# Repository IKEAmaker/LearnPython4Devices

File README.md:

# Learn to Code Python For a Device
Hej!

We have put together a few kits of a tiny microcontroller, a small LED matrix and a joystick.
There is also a [step by step guide on how to get started with coding](https://github.com/IKEAmaker/LearnPython4Devices/raw/master/Docs/LearnToCode-CompleteGuide.pdf) with this kit.
The target audience for this kit is 100% analog humans with zero coding experience.
We hope this is a fun way to get into digital creativity.

If you want to get an idea how this kit can be used to teach coding,
you can check [this 6 minute video.](https://youtu.be/odnBymFynmI)

One of the projects in the guide includes a scrolling text display:

# Build This Kit
If you can come to Maker Friday at the Co-Create lab and we'll help you out.
Most of the kit can be bought from Adafruit. We have set up a [shopping list that covers almost everything needed.](http://www.adafruit.com/wishlists/482690) The only thing you need to add is some strips of wires.

| How to build |               | 
| ------------- |:-------------:|
|This is what the kit looks like when it is built|  |
| The first step is to collect all the parts ||
| The next step is to solder the rows of pins and the LED matrix to the PCBs. There are a few videos showing how it's done: [1 Solder the microcontroller to it's rows of pins (and some general soldering tips)](https://www.youtube.com/watch?v=GbWMCBHOKaM). [2 Solder the LED matrix to it's own PCB](https://www.youtube.com/watch?v=Tg6XQbmof4U). [3 Solder a row of pins to the LED matrix PCB](https://www.youtube.com/watch?v=a5eWrJ8vEno)  ||
| When all the soldering is done, we insert the components into the breadboard and then its time to wire things up. The image to the right is a schematic showing how to connect the different signals.||
| The first wires to connect are the power wires to both the LED matrix and the Joystick. The red wire connects "3V" pin on the microcontroller with "+" pin on the LED matrix and "+5V" pin on the joystick. The black wire connects "Gnd" pin on the microcontroller with "-" pin on the LED matrix and "GND" pin on the joystick.  ||
| Next we connect the "C" pin on the LED matrix to pin "2" on the microcontroller. And the "D" pin on the LED matrix is connected to "0" pin on the microcontroller.  ||
| Lastly we connect three signals between the microcontroller and the joystick. The "VRx" pin on the joystick should be connected to the "4" pin on the microcontroller, The "VRy" pin on the joystick should be connected to the "3" pin on the microcontroller and lastly, the "SW" pin on the joystick should be connected to the "~1" pin on the microcontroller.  ||

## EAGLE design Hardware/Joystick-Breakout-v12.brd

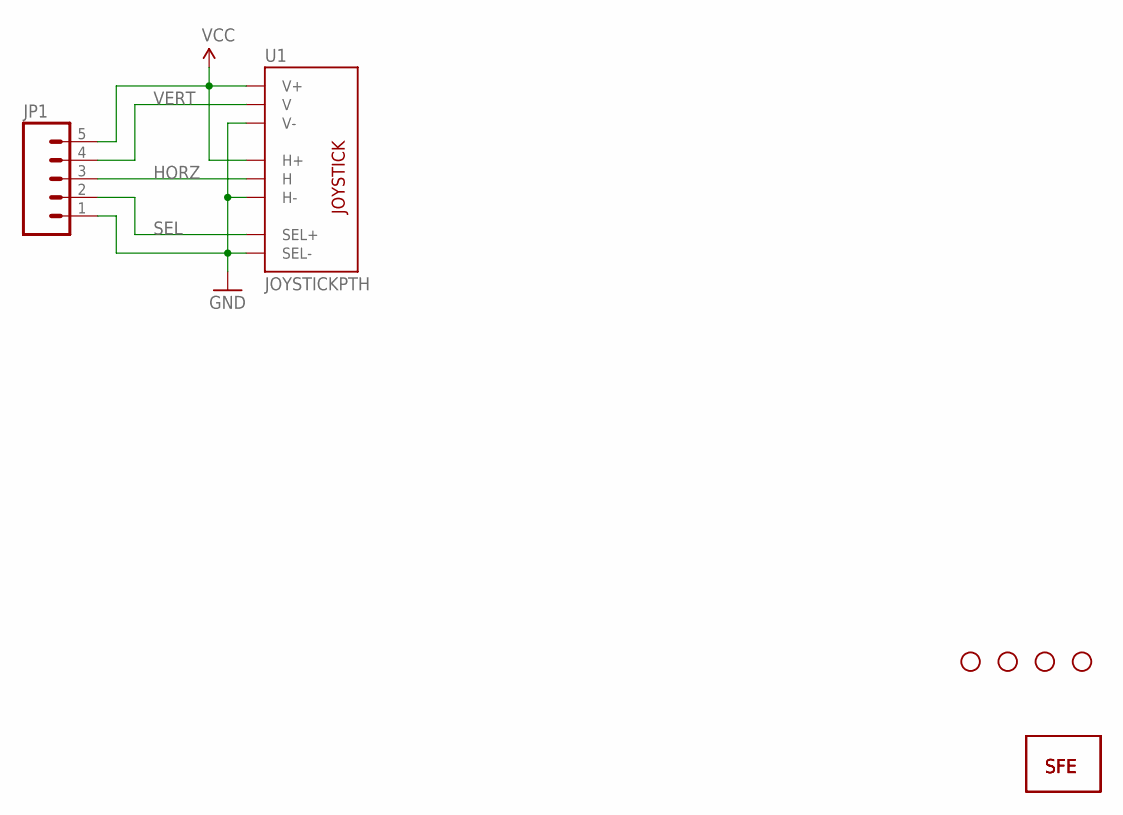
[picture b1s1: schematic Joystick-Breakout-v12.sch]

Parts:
JP1: M05PTH; 1X05
U1: JOYSTICKPTH; JOYSTICK
U$1: LOGO-SFENEW; SFE-NEW-WEBLOGO
U$2: LOGO-SFESK; SFE-LOGO-FLAME
U$3, U$4, U$5, U$6: STAND-OFF

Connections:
GND: JP1.1, U1.B2A (SEL-), U1.H3 (H-), U1.V3 (V-)
HORZ: JP1.3, U1.H2 (H)
SEL: JP1.2, U1.B1A (SEL+)
VCC: JP1.5, U1.H1 (H+), U1.V1 (V+)
VERT: JP1.4, U1.V2 (V)

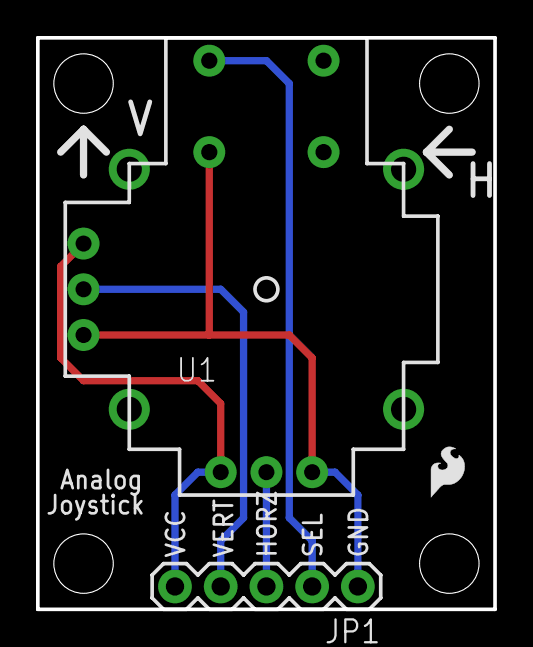
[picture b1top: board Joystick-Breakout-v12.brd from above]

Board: 2 copper layers, 25.4 x 31.8 mm, 8 parts (1 on the bottom side), 5 nets.

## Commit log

2019-02-05 Added fritz
2019-02-05 First code commit
2019-02-05 Update README.md
    new gif
2019-02-06 First version of guide
2019-02-06 New Wiring pictures
2019-02-06 soldering image
2019-02-06 added soldering video link
2019-02-07 switch to markdown
2019-02-07 rename pic
2019-02-07 rename
2019-02-07 remove resistor
2019-02-07 Assembly instructions complete
2019-02-08 started project 6 in guide
2019-02-09 more scrolling
2019-02-09 typo
2019-02-12 alpha test
2019-02-17 moving to OO, converted tinker_kit to a class
2019-02-17 update guide with OO
2019-02-17 correct initial values
2019-02-18 completed project 7
2019-02-18 new media and missed driver
2019-02-18 update after first pilot
2019-02-19 added toggle to Blink
2019-02-19 adding uml diagram for tinker_kit
2019-02-21 missing quoutes in a step in chapter 3
2019-02-26 Created using Colaboratory
2019-02-26 for collab tutorial
2019-02-26 running colab first time
2019-02-26 ResetAllRuntimesPrompt
2019-03-02 Update README.md
    added link to Adafruit shopping list.
2019-03-12 Base Plate
2019-03-14 removing calibration factors. calculated during startup instead
2019-03-15 First try on a setup utility
2019-03-15 bugfix in calibration
2019-03-15 bugfix, can now flash firmware
2019-03-17 removing unused driver. the whole SourceCodeRoot folder now fits without modification
2019-03-17 Simplifying 'kit' object instatiation
2019-03-17 New picture reflecting new filename kit.py
2019-03-24 adding kit.py
2019-03-25 cosmetics
2019-03-25 Link to feedback survey
2019-03-25 allen key
2019-03-31 add suport for max7219
2019-03-31 handle i/o for itsybitsy
2019-03-31 updating matrix text functions to works for both max7219 and ht16k33
2019-03-31 adding max7219 library and new i/o mapping
2019-03-31 added firmware for itsybitsy
2019-04-05 ooops
2019-04-08 Added 80x80 base plate
2019-04-08 started schematics for itsybitsy
2019-04-09 putting main.py back
2019-04-10 Adding Feedback sheet and correcting the project to load in main.py
2019-08-29 Added a version for printing hand outs
2020-03-03 swapped arg in project 5
2020-03-03 swapped args in project 5
